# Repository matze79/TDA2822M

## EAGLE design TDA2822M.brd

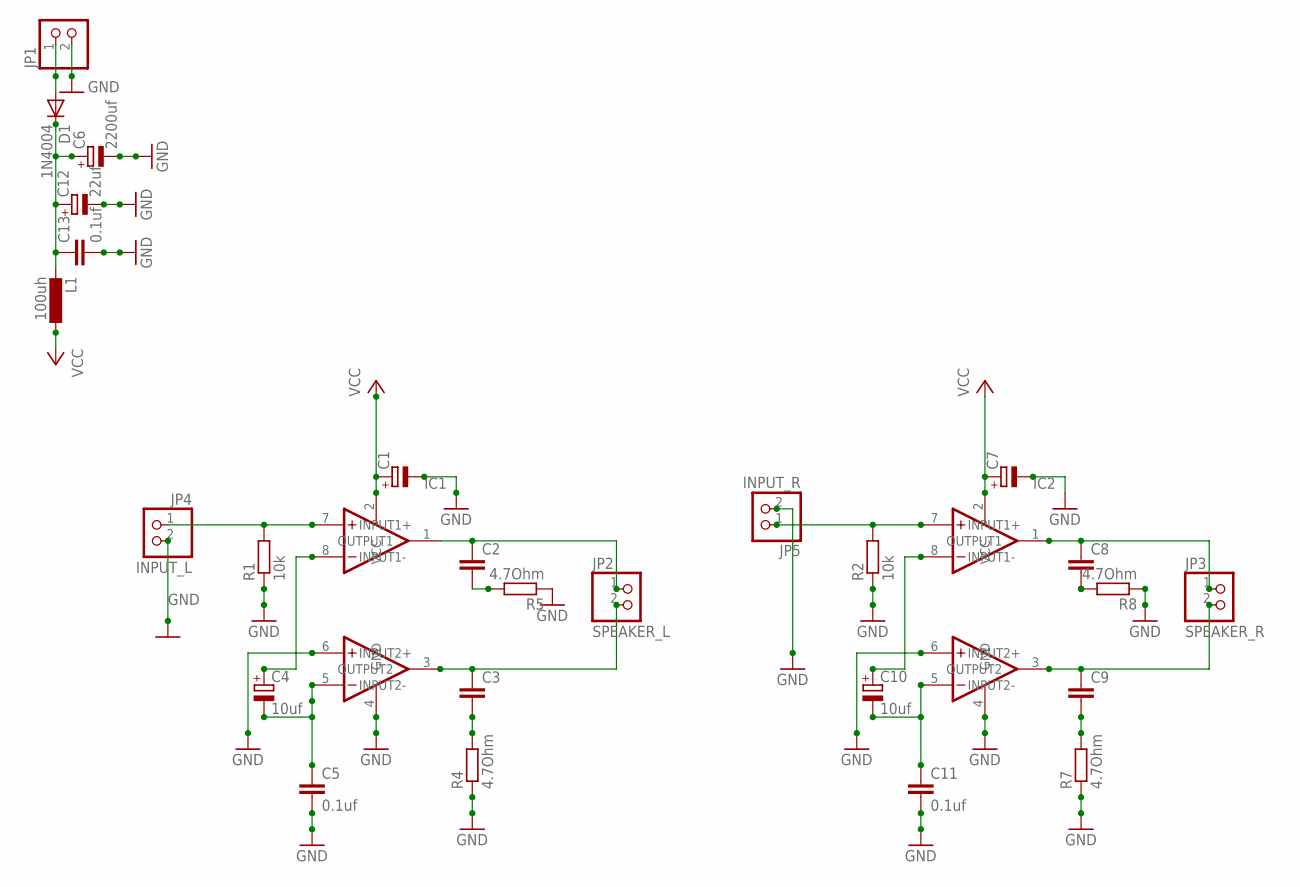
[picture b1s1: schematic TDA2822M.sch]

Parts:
C1, C7: CPOL-EUE2.5-7; E2,5-7
C2, C3, C8, C9: C-EU025_050-035X075; C025_050-035X075
C4, C10: 10uf; E2,5-7
C5, C11: 0.1uf; C025_050-035X075
C6: 2200uf; E3,5-8
C12: 22uf; E3,5-8
C13: 0.1uf; C2.5-3
D1: 1N4004; DO41-10
IC1, IC2: TDA2822M; DIL8
JP1: PINHD-1X2; 1X02
JP2: SPEAKER_L; 1X02
JP3: SPEAKER_R; 1X02
JP4: INPUT_L; 1X02
JP5: INPUT_R; 1X02
L1: 100uh; 0207/10
R1, R2: 10k; 0207/10
R4, R5, R7, R8: 4.7Ohm; 0207/10

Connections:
GND: C1.-, C5.2, C6.-, C7.-, C11.2, C12.-, C13.2, IC1.4 (GND), IC1.6 (INPUT2+), IC2.4 (GND), IC2.6 (INPUT2+), JP1.2, JP4.2, JP5.2, R1.1, R2.1, R4.1, R5.1, R7.1, R8.1
unnamed: C4.+, IC1.8 (INPUT1-)
unnamed: C4.-, C5.1, IC1.5 (INPUT2-)
unnamed: IC1.7 (INPUT1+), JP4.1, R1.2
unnamed: C6.+, C12.+, C13.1, D1.C, L1.2
unnamed: C3.1, IC1.3 (OUTPUT2), JP2.2
unnamed: C2.1, IC1.1 (OUTPUT1), JP2.1
unnamed: C3.2, R4.2
unnamed: C2.2, R5.2
unnamed: D1.A, JP1.1
unnamed: C9.1, IC2.3 (OUTPUT2), JP3.2
unnamed: C8.1, IC2.1 (OUTPUT1), JP3.1
unnamed: C9.2, R7.2
unnamed: C8.2, R8.2
unnamed: C10.+, IC2.8 (INPUT1-)
unnamed: C10.-, C11.1, IC2.5 (INPUT2-)
unnamed: IC2.7 (INPUT1+), JP5.1, R2.2
VCC: C1.+, C7.+, IC1.2 (VCC), IC2.2 (VCC), L1.1

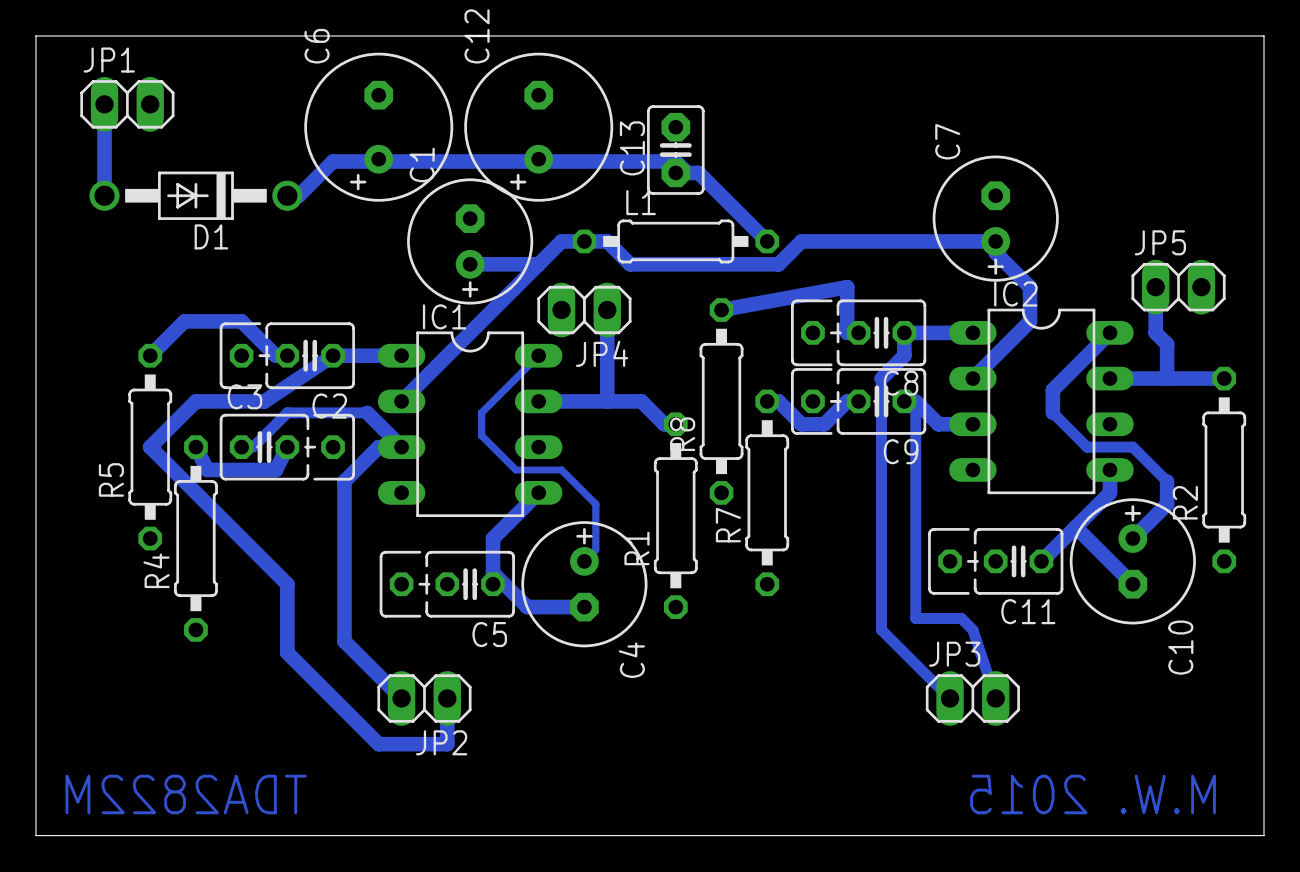
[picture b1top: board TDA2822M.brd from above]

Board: 2 copper layers, 68.2 x 44.4 mm, 28 parts (0 on the bottom side), 18 nets.

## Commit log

2020-10-07 Add files via upload
    The values for the capacitors are the same as in the datasheet.
